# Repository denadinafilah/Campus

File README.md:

# Campus Projects

A collection of academic projects, coursework, and technical experiments completed during my undergraduate studies in Physics at Universitas Pendidikan Indonesia.

This repository serves as documentation of my academic work, practical experience, and technical development throughout my university journey.

## About

My academic background in Physics has provided opportunities to explore various areas, including electronics, computational methods, experimental work, and engineering-related applications.

This repository will continue to grow as I document more projects and learning experiences.

Author: Dena Dinafilah
Background: Physics Graduate – Universitas Pendidikan Indonesia

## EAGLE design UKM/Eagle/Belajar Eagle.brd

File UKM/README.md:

# KOMPOR UPI – Robotics & Automation Community

## Overview

KOMPOR UPI (Komunitas Mahasiswa Pecinta Robot, Otomasi, dan Robotika Universitas Pendidikan Indonesia) is a student community focused on exploring robotics, automation, and related technologies.

This experience provided an opportunity to learn fundamental electronic and control system concepts through technical exploration and collaborative learning.

## Learning Areas

- **Sensors:** Understanding sensor principles and their applications in detecting environmental conditions.
- **Actuators:** Exploring actuators as components that convert control signals into physical actions.
- **Microcontrollers:** Learning the fundamentals of microcontroller-based systems.
- **Serial Communication:** Exploring communication between electronic devices and microcontrollers.

## Key Learning Outcomes

- Developed foundational knowledge of robotics and automation systems.
- Gained exposure to electronic components and their practical applications.
- Explored the relationship between sensing, processing, and actuation.
- Improved technical exploration and collaborative learning skills.

## Organization

**KOMPOR UPI**  
Universitas Pendidikan Indonesia

**Field:** Robotics, Automation & Electronics

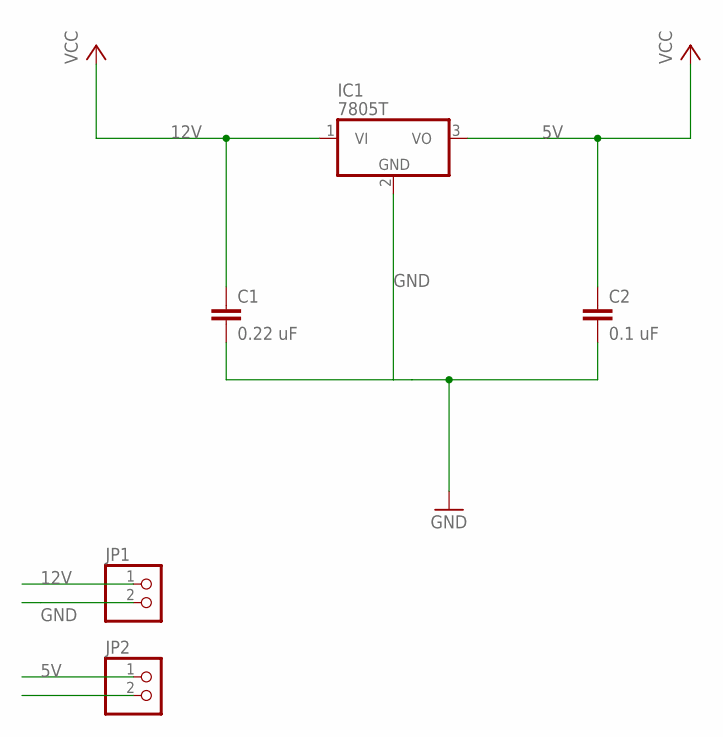
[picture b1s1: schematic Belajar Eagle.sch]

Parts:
C1: 0.22 uF; C050-075X075
C2: 0.1 uF; C050-075X075
IC1: 7805T; TO220H
JP1, JP2: PINHD-1X2; 1X02

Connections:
5V: C2.1, IC1.3 (VO), JP2.1
12V: C1.1, IC1.1 (VI), JP1.1
GND: C1.2, C2.2, IC1.2 (GND), JP1.2, JP2.2

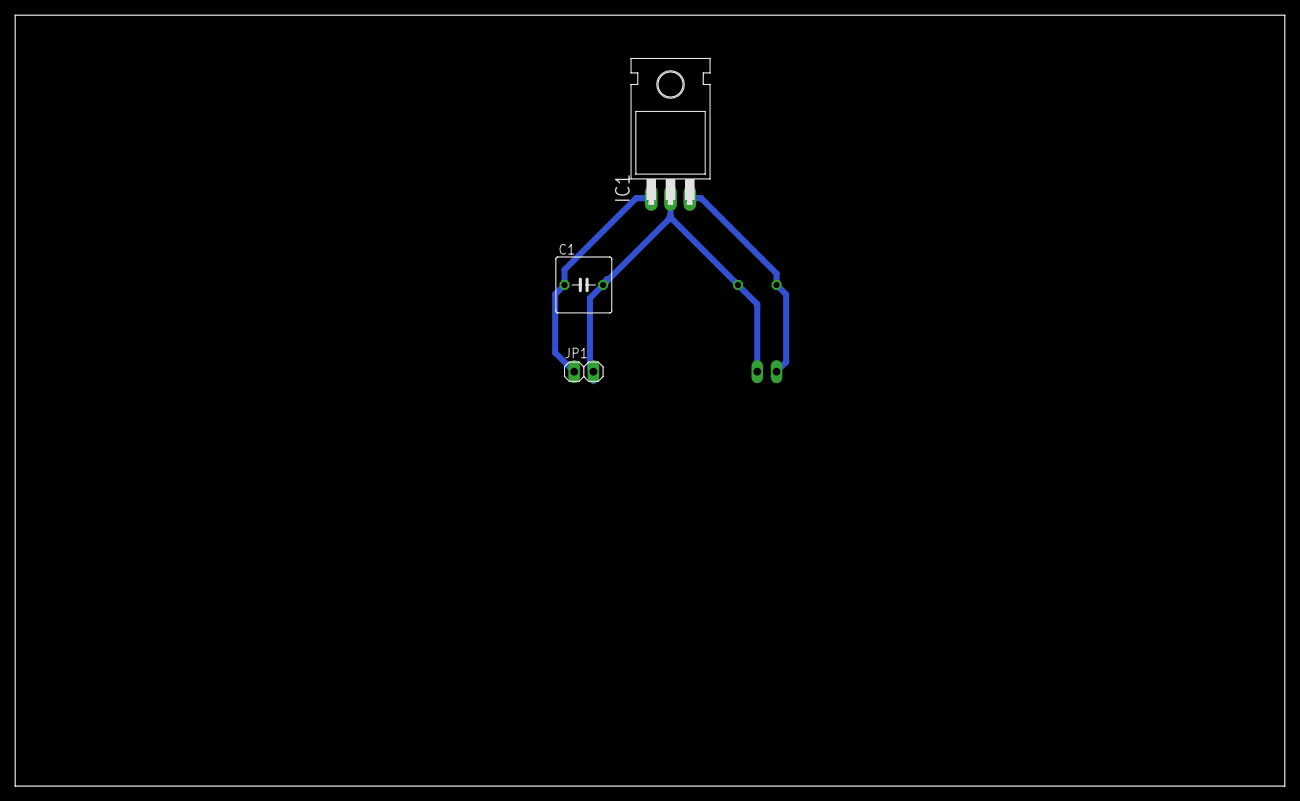
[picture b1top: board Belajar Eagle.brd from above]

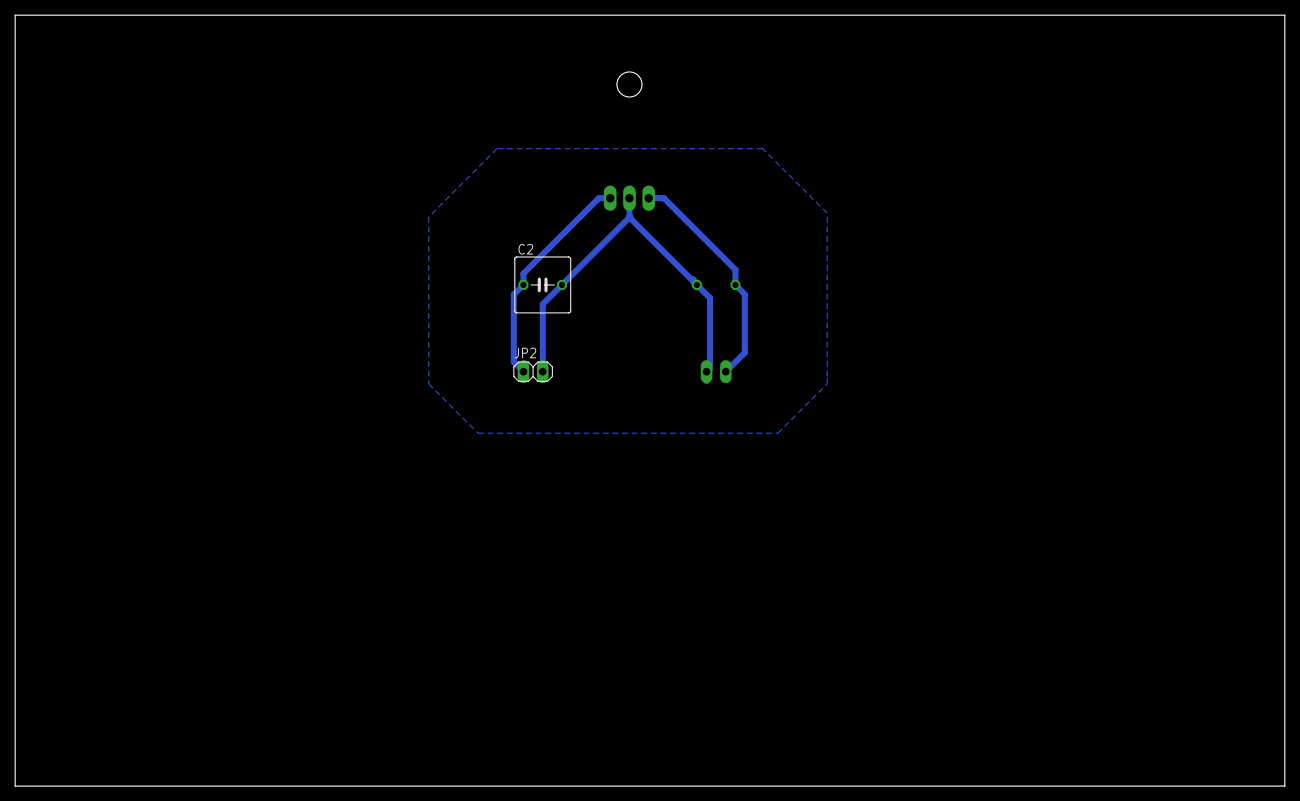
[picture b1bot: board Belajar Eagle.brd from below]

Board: 2 copper layers, 167.3 x 101.6 mm, 5 parts (2 on the bottom side), 3 nets.
